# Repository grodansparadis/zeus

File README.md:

# zeus
Ethernet carrier board for VSCP
<hr>

This project is part of the <a href="http://www.vscp.org">VSCP (Very Simple Control Protocol) project</a>. 

<hr>

This project is licensed under the 
<a href="http://creativecommons.org/licenses/by-nc-sa/3.0/">Creative Commons open source license Attribution-NonCommercial-ShareAlike 3.0 Unported</a>. 
Other license options are available by conacting <a href="malto:info@grodansparadis.com">Paradis of the Frog AB</a>

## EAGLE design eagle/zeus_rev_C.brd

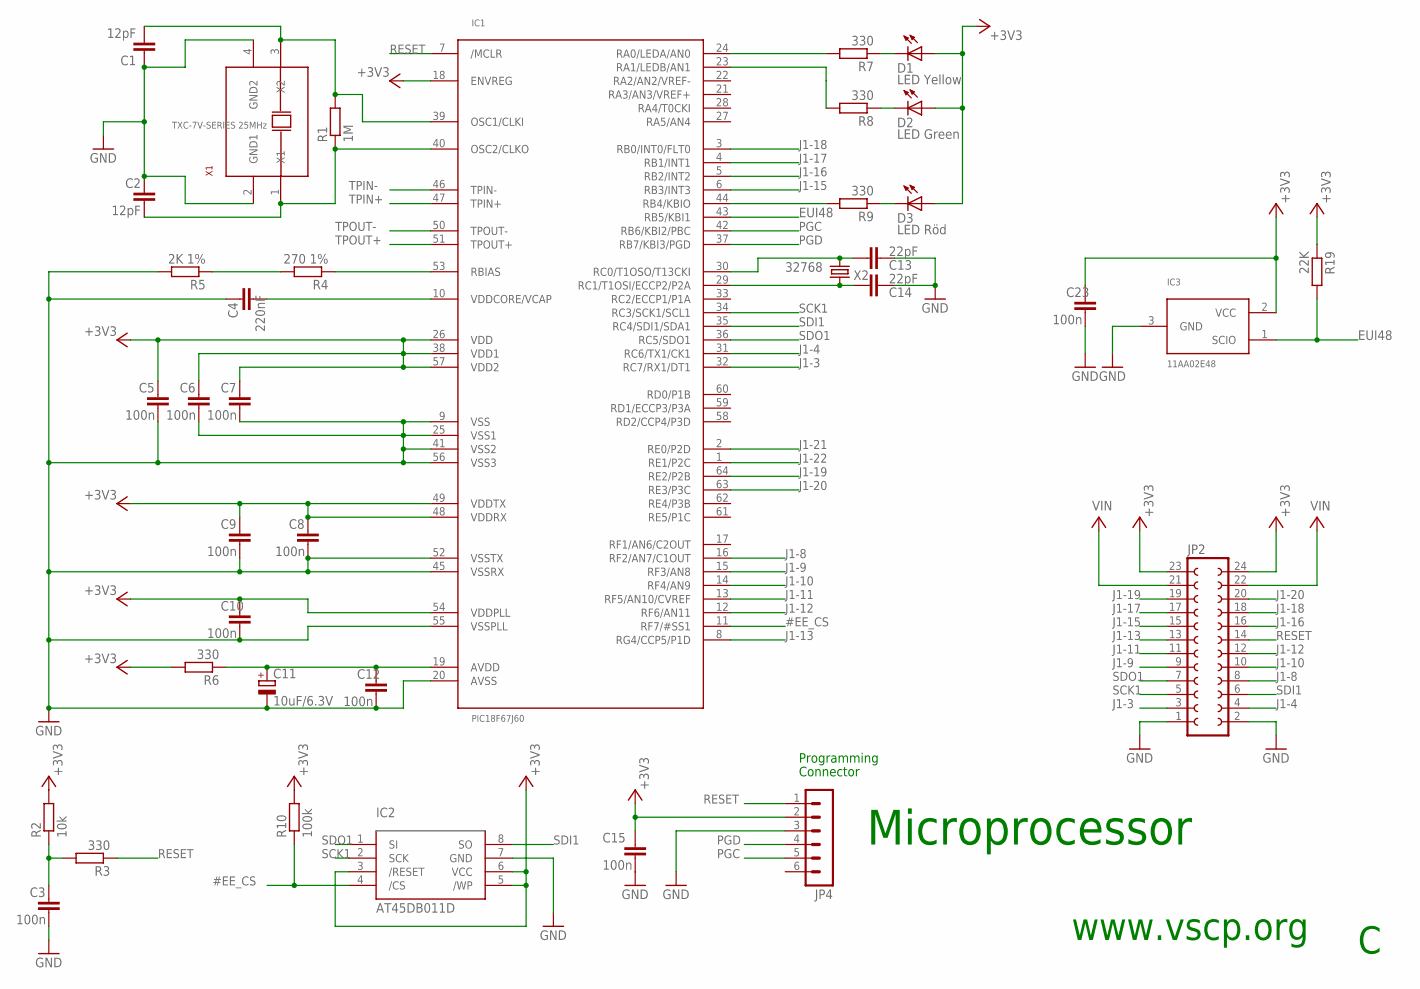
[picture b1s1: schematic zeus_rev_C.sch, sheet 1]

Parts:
C1, C2: 12pF; C0805
C3, C5, C6, C7, C8, C9, C10, C12, C15, C23: 100n; C0805
C4: 220nF; C0805
C11: 10uF/6.3V; SMC_P
C13, C14: 22pF; C0805
D1: LED Yellow; C2012
D2: LED Green; C2012
D3: LED Röd; C2012
IC1: PIC18F67J60; TQFP64-10X10
IC2: AT45DB011D; SOP8W
IC3: 11AA02E48; SOT23
JP2: FE12-2
JP4: MA06-1
R1: 1M; M0805
R2: 10k; M0805
R3, R6, R7, R8, R9: 330; M0805
R4: 270 1%; M0805
R5: 2K 1%; M0805
R10: 100k; M0805
R19: 22K; M0805
X1: TXC-7V-SERIES 25MHz; TXC-7V-SERIES
X2: 32768; TC26H

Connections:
#EE_CS: IC1.11 (RF7/#SS1), IC2.4 (/CS), R10.1
+3V3: C5.1, C6.1, C7.1, C8.1, C9.1, C10.1, C15.1, C23.1, D1.1 (A), D2.1 (A), D3.1 (A), IC1.18 (ENVREG), IC1.26 (VDD), IC1.38 (VDD1), IC1.48 (VDDRX), IC1.49 (VDDTX), IC1.54 (VDDPLL), IC1.57 (VDD2), IC2.3 (/RESET), IC2.5 (/WP), IC2.6 (VCC), IC3.2 (VCC), JP2.23, JP2.24, JP4.2, R2.2, R6.2, R10.2, R19.1; also elsewhere on the board
EUI48: IC1.43 (RB5/KBI1), IC3.1 (SCIO), R19.2
GND: C1.1, C2.1, C3.2, C4.1, C5.2, C6.2, C7.2, C8.2, C9.2, C10.2, C11.-, C12.2, C13.1, C14.1, C15.2, C23.2, IC1.9 (VSS), IC1.20 (AVSS), IC1.25 (VSS1), IC1.41 (VSS2), IC1.45 (VSSRX), IC1.52 (VSSTX), IC1.55 (VSSPLL), IC1.56 (VSS3), IC2.7 (GND), IC3.3 (GND), JP2.1, JP2.2, JP4.3, R5.2, X1.2 (GND1), X1.4 (GND2); also elsewhere on the board
J1-3: IC1.32 (RC7/RX1/DT1), JP2.3; also elsewhere on the board
J1-4: IC1.31 (RC6/TX1/CK1), JP2.4; also elsewhere on the board
J1-8: IC1.16 (RF2/AN7/C1OUT), JP2.8
J1-9: IC1.15 (RF3/AN8), JP2.9
J1-10: IC1.14 (RF4/AN9), JP2.10
J1-11: IC1.13 (RF5/AN10/CVREF), JP2.11
J1-12: IC1.12 (RF6/AN11), JP2.12
J1-13: IC1.8 (RG4/CCP5/P1D), JP2.13
J1-15: IC1.6 (RB3/INT3), JP2.15
J1-16: IC1.5 (RB2/INT2), JP2.16
J1-17: IC1.4 (RB1/INT1), JP2.17
J1-18: IC1.3 (RB0/INT0/FLT0), JP2.18
J1-19: IC1.64 (RE2/P2B), JP2.19
J1-20: IC1.63 (RE3/P3C), JP2.20
J1-21: IC1.2 (RE0/P2D)
J1-22: IC1.1 (RE1/P2C)
unnamed: C1.2, IC1.39 (OSC1/CLKI), R1.2, X1.3 (X2)
unnamed: C2.2, IC1.40 (OSC2/CLKO), R1.1, X1.1 (X1)
unnamed: IC1.53 (RBIAS), R4.1
unnamed: R4.2, R5.1
unnamed: C14.2, IC1.29 (RC1/T1OSI/ECCP2/P2A), X2.2
unnamed: C3.1, R2.1, R3.2
unnamed: C4.2, IC1.10 (VDDCORE/VCAP)
unnamed: C13.2, IC1.30 (RC0/T1OSO/T13CKI), X2.1
unnamed: IC1.24 (RA0/LEDA/AN0), R7.2
unnamed: IC1.23 (RA1/LEDB/AN1), R8.2
unnamed: IC1.44 (RB4/KBIO), R9.2
unnamed: D3.2 (C), R9.1
unnamed: D2.2 (C), R8.1
unnamed: D1.2 (C), R7.1
unnamed: C11.+, C12.1, IC1.19 (AVDD), R6.1
PGC: IC1.42 (RB6/KBI2/PBC), JP4.5
PGD: IC1.37 (RB7/KBI3/PGD), JP4.4
RESET: IC1.7 (/MCLR), JP2.14, JP4.1, R3.1
SCK1: IC1.34 (RC3/SCK1/SCL1), IC2.2 (SCK), JP2.5
SDI1: IC1.35 (RC4/SDI1/SDA1), IC2.8 (SO), JP2.6
SDO1: IC1.36 (RC5/SDO1), IC2.1 (SI), JP2.7
TPIN+: IC1.47 (TPIN+); also elsewhere on the board
TPIN-: IC1.46 (TPIN-); also elsewhere on the board
TPOUT+: IC1.51 (TPOUT+); also elsewhere on the board
TPOUT-: IC1.50 (TPOUT-); also elsewhere on the board
V+: JP2.21, JP2.22; also elsewhere on the board

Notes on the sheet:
Programming
Connector
Microprocessor
www.vscp.org

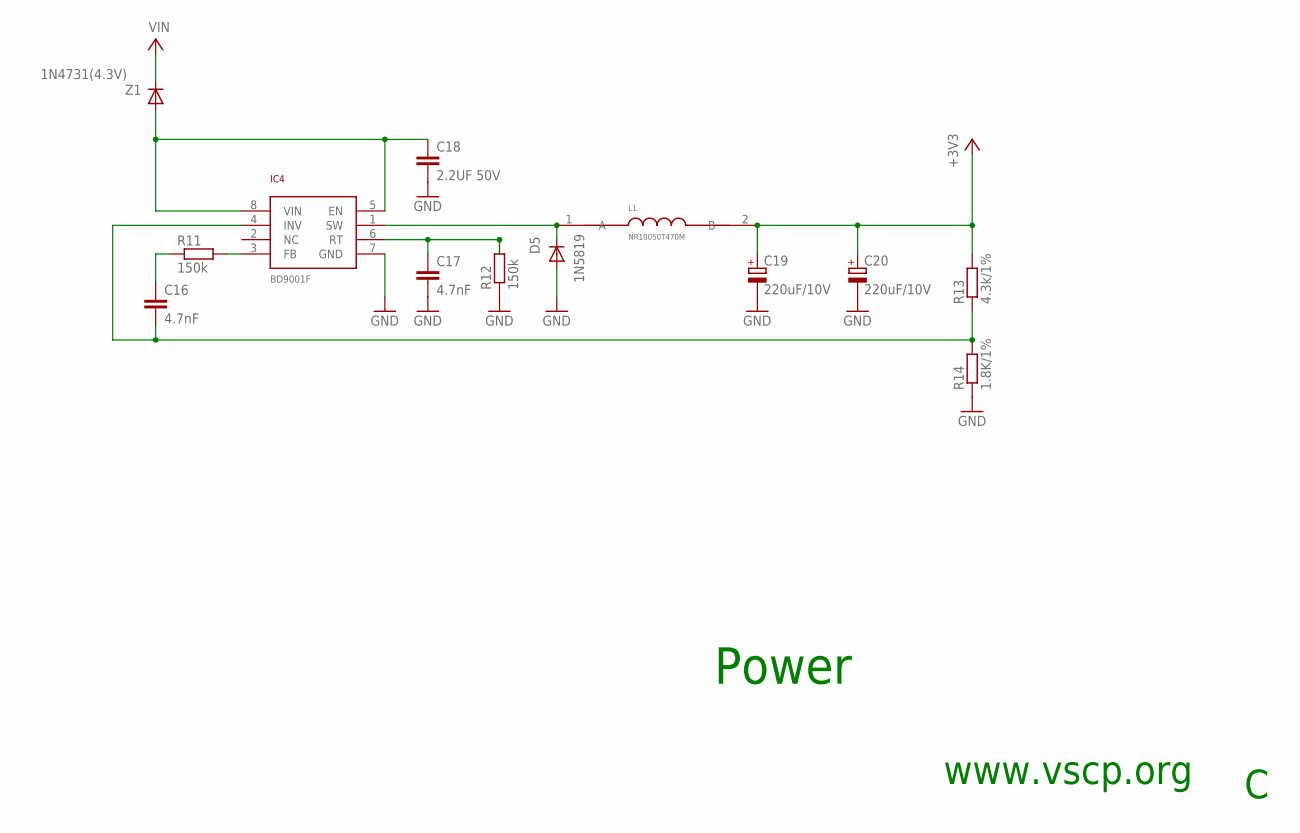
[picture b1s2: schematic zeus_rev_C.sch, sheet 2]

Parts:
C16, C17: 4.7nF; C0805
C18: 2.2UF 50V; C2012
C19, C20: 220uF/10V; SMC_C
D5: 1N5819; SOD-123
IC4: BD9001F; SOP8
L1: NR10050T470M
R11, R12: 150k; M0805
R13: 4.3k/1%; M0805
R14: 1.8K/1%; M0805
Z1: 1N4731(4.3V); 1N4731

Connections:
+3V3: C19.+, C20.+, L1.2 (B), R13.2; also elsewhere on the board
GND: C17.2, C18.2, C19.-, C20.-, D5.A, IC4.7 (GND), R12.1, R14.1; also elsewhere on the board
unnamed: IC4.3 (FB), R11.2
unnamed: C16.1, R11.1
unnamed: C16.2, IC4.4 (INV), R13.1, R14.2
unnamed: C17.1, IC4.6 (RT), R12.2
unnamed: C18.1, IC4.5 (EN), IC4.8 (VIN), Z1.A
unnamed: D5.C, IC4.1 (SW), L1.1 (A)
V+: Z1.C; also elsewhere on the board

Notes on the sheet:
Power
www.vscp.org

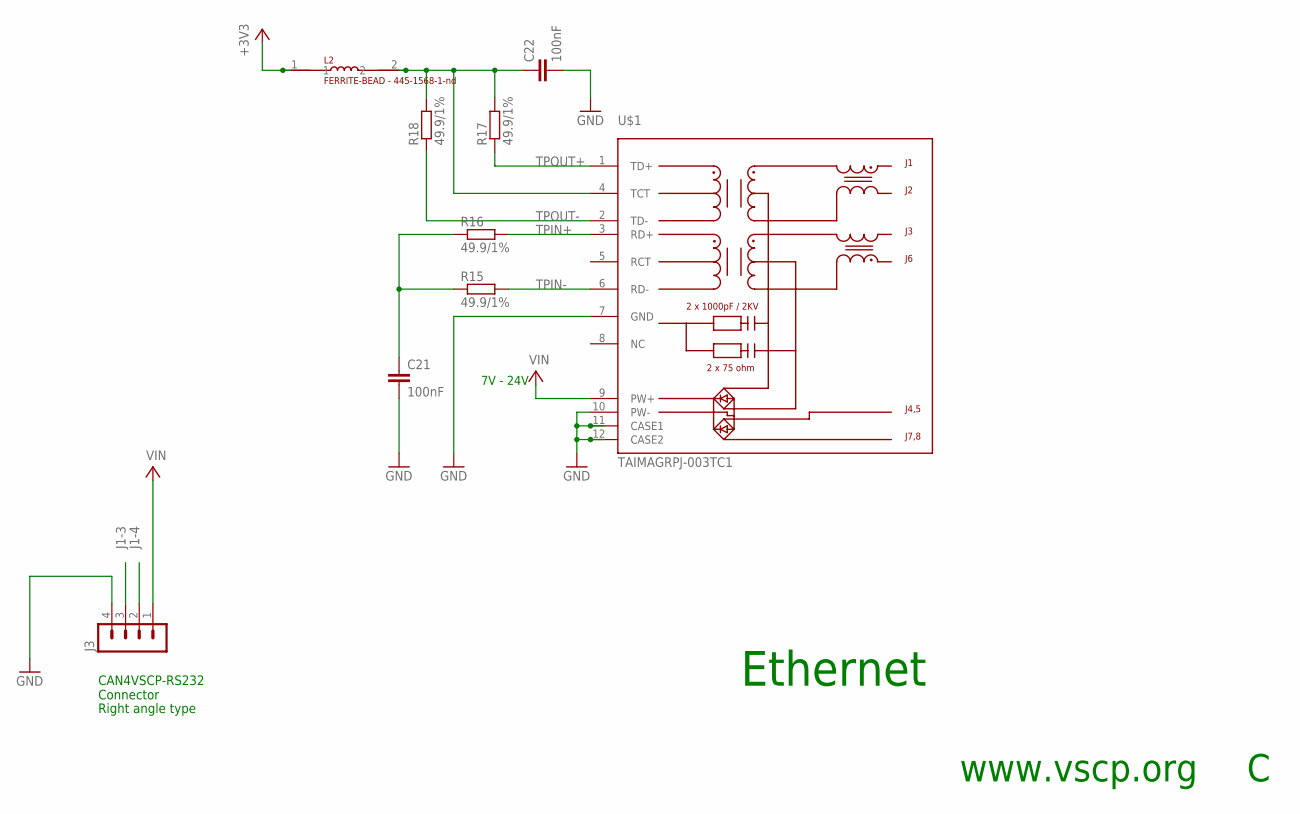
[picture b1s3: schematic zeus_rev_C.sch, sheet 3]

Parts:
C21, C22: 100nF; C0805
J3: MA04-1
L2: FERRITE-BEAD - 445-1568-1-nd; 0805
R15, R16, R17, R18: 49.9/1%; M0805
U$1: TAIMAGRPJ-003TC1; TAIMAGRJP-003TC1

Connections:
+3V3: L2.1; also elsewhere on the board
GND: C21.2, C22.2, J3.4, U$1.7 (GND), U$1.10 (PW-), U$1.11 (CASE1), U$1.12 (CASE2); also elsewhere on the board
J1-3: J3.3; also elsewhere on the board
J1-4: J3.2; also elsewhere on the board
unnamed: C21.1, R15.1, R16.1
unnamed: C22.1, L2.2, R17.2, R18.2, U$1.4 (TCT)
TPIN+: R16.2, U$1.3 (RD+); also elsewhere on the board
TPIN-: R15.2, U$1.6 (RD-); also elsewhere on the board
TPOUT+: R17.1, U$1.1 (TD+); also elsewhere on the board
TPOUT-: R18.1, U$1.2 (TD-); also elsewhere on the board
V+: J3.1, U$1.9 (PW+); also elsewhere on the board

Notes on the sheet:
Ethernet
7V - 24V
www.vscp.org
CAN4VSCP-RS232 Connector
Right angle type

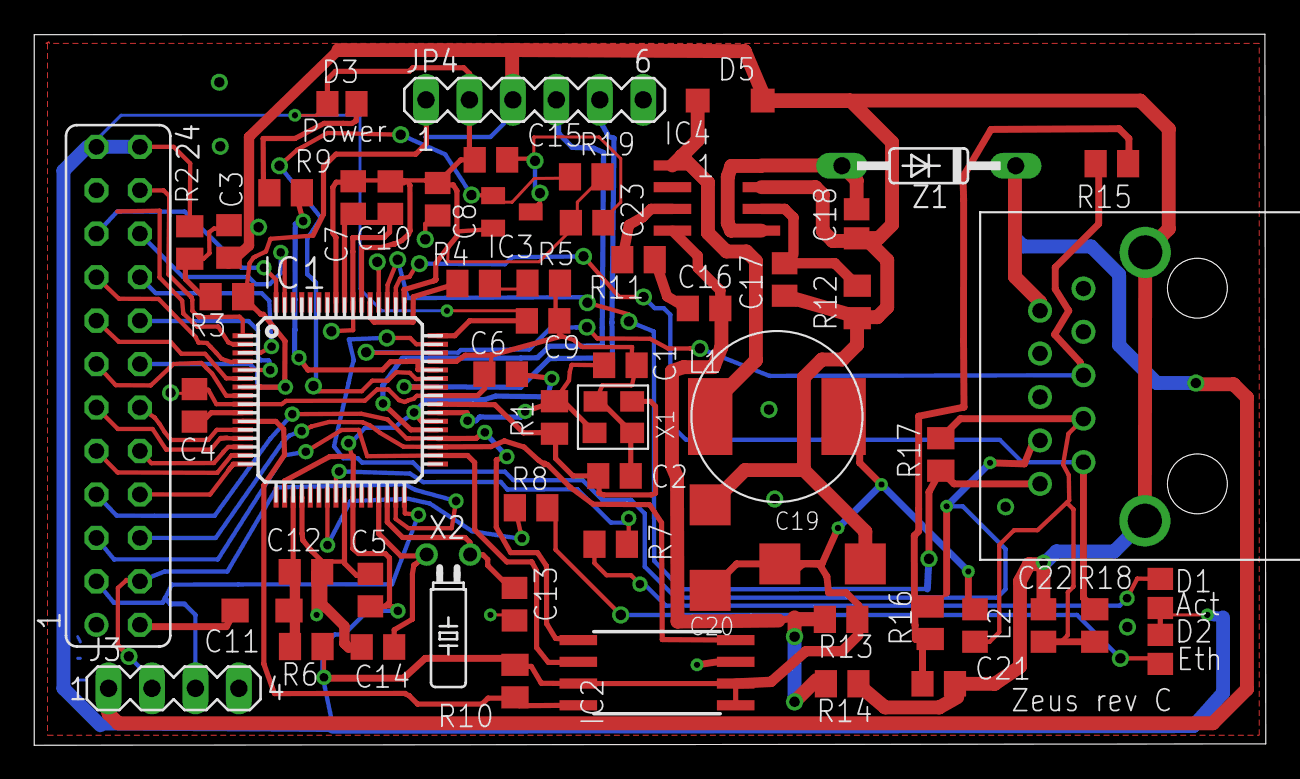
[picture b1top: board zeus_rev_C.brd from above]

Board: 2 copper layers, 72.0 x 41.6 mm, 59 parts (0 on the bottom side), 52 nets.

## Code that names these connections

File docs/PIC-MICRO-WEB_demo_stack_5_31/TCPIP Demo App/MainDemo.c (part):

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	// Inputs
	RPINR19bits.U2RXR = 19;			//U2RX = RP19
	RPINR22bits.SDI2R = 20;			//SDI2 = RP20
	RPINR20bits.SDI1R = 17;			//SDI1 = RP17
	
	// Outputs
	RPOR12bits.RP25R = U2TX_IO;		//RP25 = U2TX  
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	RPOR7bits.RP15R = SCK1OUT_IO; 	//RP15 = SCK1
	RPOR8bits.RP16R = SDO1_IO;		//RP16 = SDO1
	
	AD1PCFG = 0xFFFF;				//All digital inputs - POT and Temp are on same pin as SDO1/SDI1, which is needed for ENC28J60 commnications

	__builtin_write_OSCCONL(OSCCON | 0x40); // Lock PPS
#endif
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
	// Inputs
	RPINR19bits.U2RXR = 11;	// U2RX = RP11
	RPINR20bits.SDI1R = 0;	// SDI1 = RP0
	RPINR0bits.INT1R = 34;	// Assign RE9/RPI34 to INT1 (input) for MRF24WB0M Wi-Fi PICtail Plus interrupt
	
	// Outputs
	RPOR8bits.RP16R = 5;	// RP16 = U2TX
	RPOR1bits.RP2R = 8; 	// RP2 = SCK1
	RPOR0bits.RP1R = 7;		// RP1 = SDO1

	__builtin_write_OSCCONL(OSCCON | 0x40); // Lock PPS
#endif
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	__builtin_write_OSCCONL(OSCCON & 0xBF);  // Unlock PPS
	
	// Configure SPI1 PPS pins (ENC28J60/ENCX24J600/MRF24WB0M or other PICtail Plus cards)
	RPOR0bits.RP0R = 8;		// Assign RP0 to SCK1 (output)
	RPOR7bits.RP15R = 7;	// Assign RP15 to SDO1 (output)
	RPINR20bits.SDI1R = 23;	// Assign RP23 to SDI1 (input)

	// Configure SPI2 PPS pins (25LC256 EEPROM on Explorer 16)
	RPOR10bits.RP21R = 11;	// Assign RG6/RP21 to SCK2 (output)
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	
	// Configure UART2 PPS pins (MAX3232 on Explorer 16)
	#if !defined(ENC100_INTERFACE_MODE) || (ENC100_INTERFACE_MODE == 0) || defined(ENC100_PSP_USE_INDIRECT_RAM_ADDRESSING)
	RPINR19bits.U2RXR = 10;	// Assign RF4/RP10 to U2RX (input)
	RPOR8bits.RP17R = 5;	// Assign RF5/RP17 to U2TX (output)
	#endif
	
	// Configure INT1 PPS pin (MRF24WB0M Wi-Fi PICtail Plus interrupt signal when in SPI slot 1)
	RPINR0bits.INT1R = 33;	// Assign RE8/RPI33 to INT1 (input)

	// Configure INT3 PPS pin (MRF24WB0M Wi-Fi PICtail Plus interrupt signal when in SPI slot 2)
	RPINR1bits.INT3R = 40;	// Assign RC3/RPI40 to INT3 (input)

	__builtin_write_OSCCONL(OSCCON | 0x40); // Lock PPS
#endif
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	RPINR22bits.SDI2R = 26;	// Assign RG7/RP26 to SDI2 (input)
	
	// Configure UART2 PPS pins (MAX3232 on Explorer 16)
	RPINR19bits.U2RXR = 10;	// Assign RF4/RP10 to U2RX (input)
	RPOR8bits.RP17R = 5;	// Assign RF5/RP17 to U2TX (output)
	
	// Configure INT3 PPS pin (MRF24WB0M PICtail Plus interrupt signal)
	RPINR1bits.INT3R = 36;	// Assign RA14/RPI36 to INT3 (input)
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
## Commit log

2015-08-28 Moved documents from private project to public
2015-12-17 Updated readme and license
2015-12-17 added docs

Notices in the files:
docs/PIC-MICRO-WEB_demo_stack_5_31/TCPIP Demo App/MainDemo.c:
Copyright (C) 2002-2010 Microchip Technology Inc.  All rights
